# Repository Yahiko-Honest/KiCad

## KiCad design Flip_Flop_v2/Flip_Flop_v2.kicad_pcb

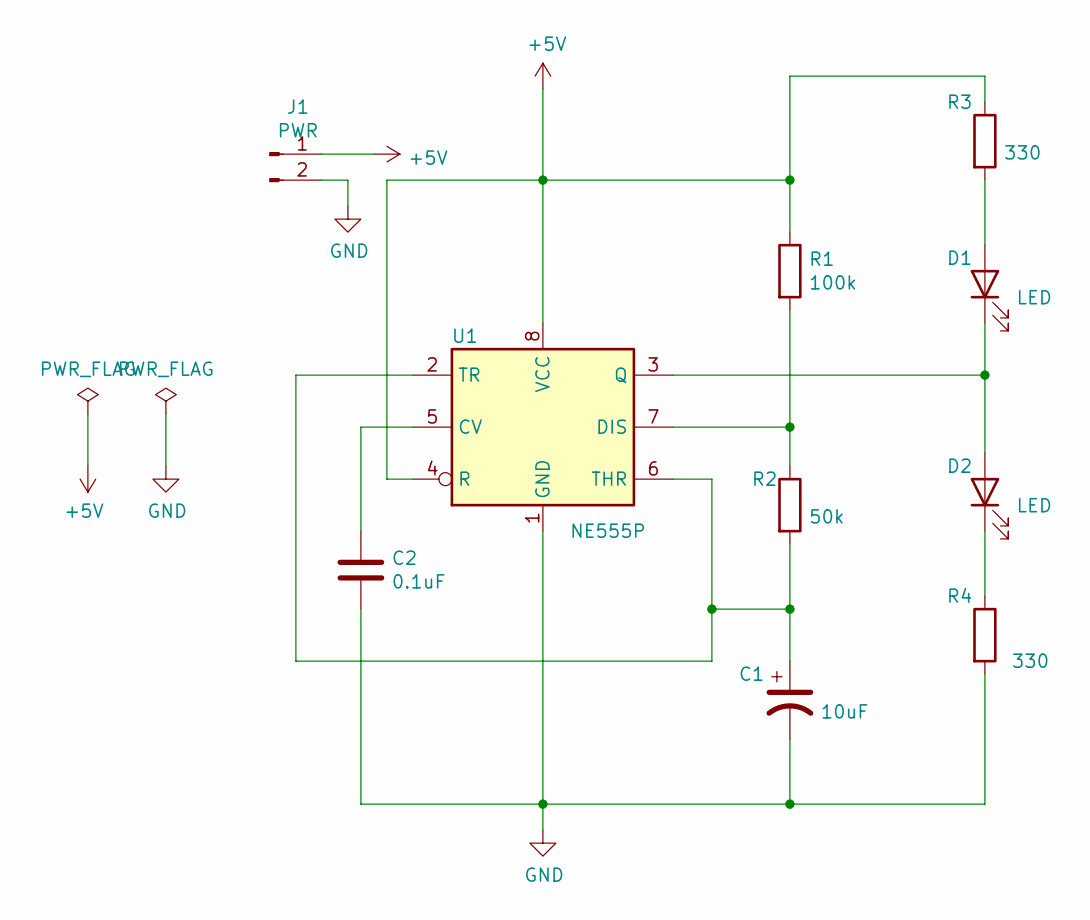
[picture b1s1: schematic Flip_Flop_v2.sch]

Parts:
C1: 10uF; CP_Radial_D6.3mm_P2.50mm
C2: 0.1uF; C_Disc_D3.0mm_W2.0mm_P2.50mm
D1, D2: LED; LED_D3.0mm
J1: PWR; Molex_KK-254_AE-6410-02A_1x02_P2.54mm_Vertical
R1: 100k; R_Axial_DIN0204_L3.6mm_D1.6mm_P5.08mm_Horizontal
R2: 50k; R_Axial_DIN0204_L3.6mm_D1.6mm_P5.08mm_Horizontal
R3, R4: 330; R_Axial_DIN0204_L3.6mm_D1.6mm_P5.08mm_Horizontal
U1: NE555P; DIP-8_W7.62mm

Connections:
+5V: J1.1, R1.1, R3.1, U1.4 (R), U1.8 (VCC)
GND: C1.2, C2.2, J1.2, R4.2, U1.1 (GND)
unnamed: C1.1, R2.2, U1.2 (TR), U1.6 (THR)
unnamed: C2.1, U1.5 (CV)
unnamed: D1.1 (K), D2.2 (A), U1.3 (Q)
unnamed: D1.2 (A), R3.2
unnamed: D2.1 (K), R4.1
unnamed: R1.2, R2.1, U1.7 (DIS)

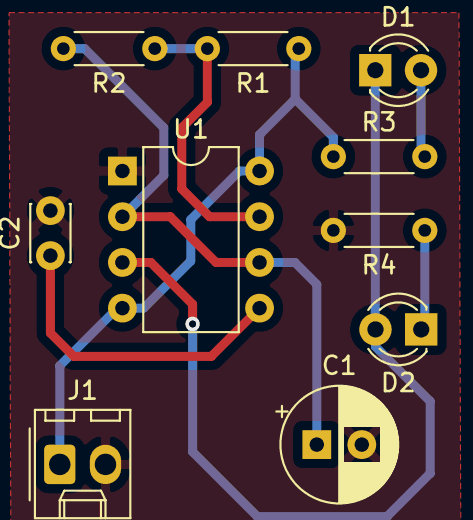
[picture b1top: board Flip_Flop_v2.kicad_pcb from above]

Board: 2 copper layers, 10 parts (0 on the bottom side), 8 nets.
